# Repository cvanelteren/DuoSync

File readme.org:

* Welcome to Duosync - a BLE wireless split keyboard powered by ZMK
The keyboard is designed by me, and is a spirtual successor to [[https://github.com/cvanelteren/Elanor/][Elanor]].

[[file:./figures/duosync.jpg]]

* Bill Of Materials

|------------------------------------+----------+------------------|
| Item                               | Quantity | Price indication |
|------------------------------------+----------+------------------|
| XIAO BLE SEEED                     |        2 | 15$              |
| Kailh/Gateron hotswappable sockets |       52 | 12$              |
| Duosync PCB                        |        2 | 5$               |
| Keyswitches                        |       52 | 30$              |
| Battery Lithium ion 3.7V           |        2 | 15$              |
| Case                               |        2 | Depends ;-)       |
|------------------------------------+----------+------------------|

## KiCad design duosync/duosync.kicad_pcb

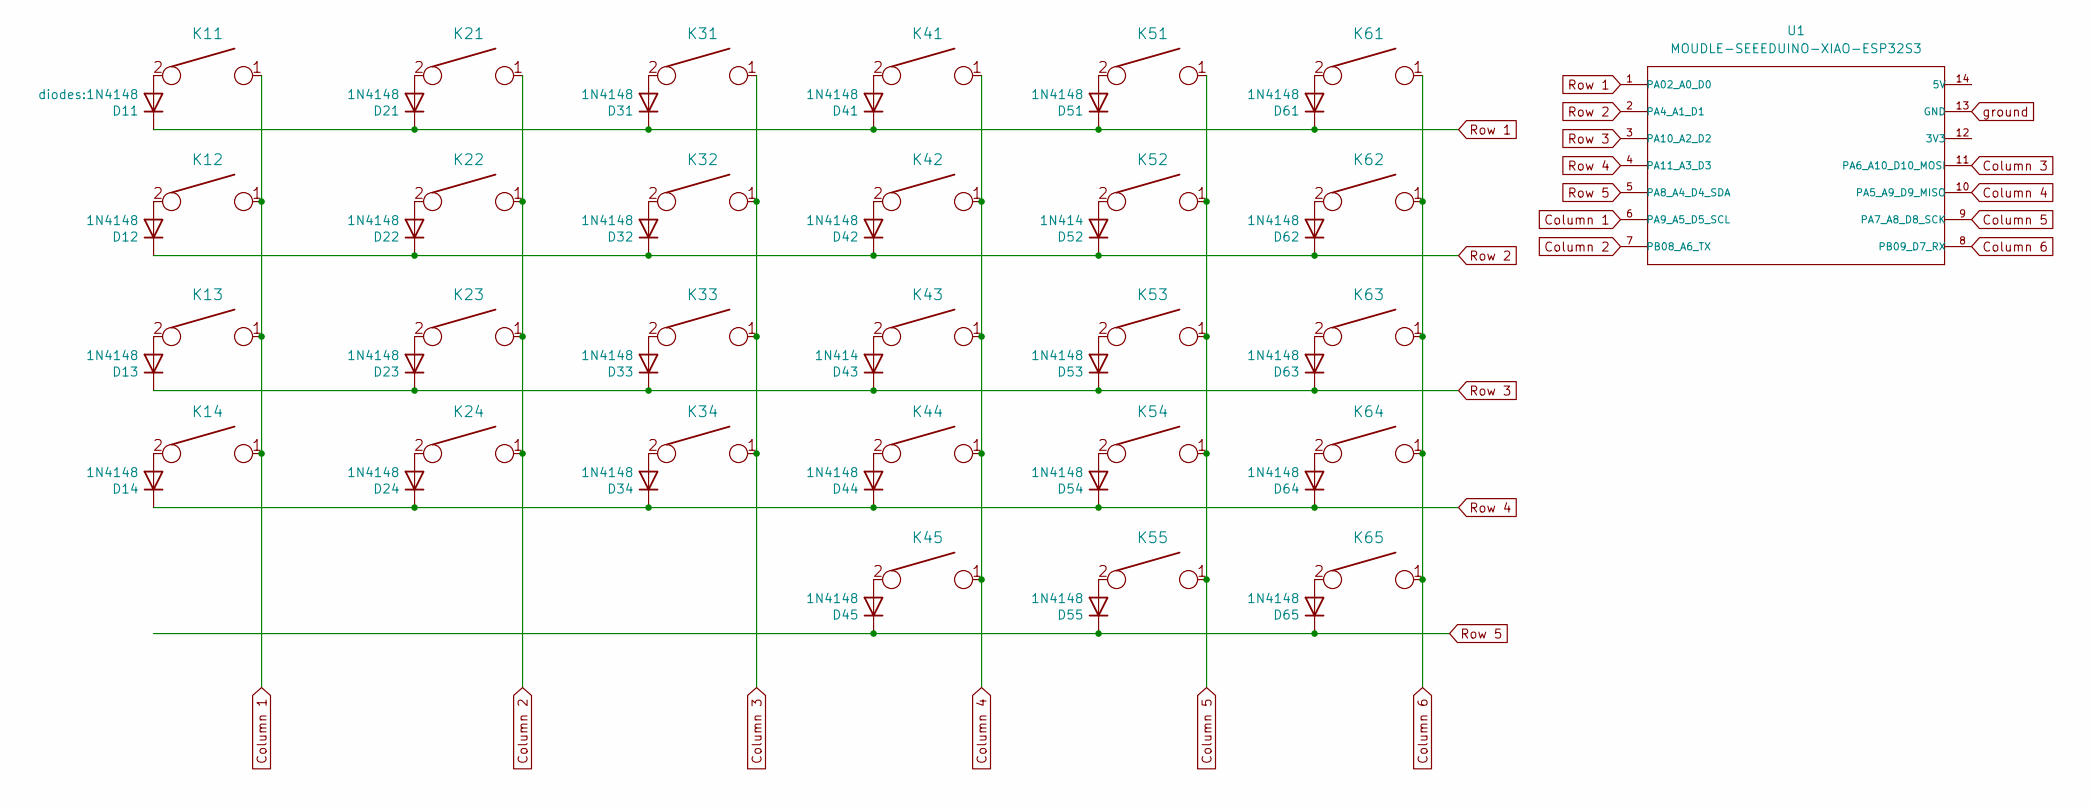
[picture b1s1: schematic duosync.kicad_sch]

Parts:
D11: diodes:1N4148; D3_TH_SMD_v2
D12, D13, D14, D21, D22, D23, D24, D31, D32, D33, D34, D41, D42, D44, D45, D51, D53, D54, D55, D61, D62, D63, D64, D65: 1N4148; D3_TH_SMD_v2
D43, D52: 1N414; D3_TH_SMD_v2
K11, K12, K13, K14, K21, K22, K23, K24, K31, K32, K33, K34, K41, K42, K43, K44, K45, K51, K52, K53, K54, K55, K61, K62, K63, K64: key; CherryMX_Choc_Hotswap
K65: key; CherryMX_Choc_Hotswap_1.5u
U1: MOUDLE-SEEEDUINO-XIAO-ESP32S3; XIAO-Generic-Hybrid-14P-2.54-21X17.8MM

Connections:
Column 1: K11.1, K12.1, K13.1, K14.1, U1.6 (PA9_A5_D5_SCL)
Column 2: K21.1, K22.1, K23.1, K24.1, U1.7 (PB08_A6_TX)
Column 3: K31.1, K32.1, K33.1, K34.1, U1.11 (PA6_A10_D10_MOSI)
Column 4: K41.1, K42.1, K43.1, K44.1, K45.1, U1.10 (PA5_A9_D9_MISO)
Column 5: K51.1, K52.1, K53.1, K54.1, K55.1, U1.9 (PA7_A8_D8_SCK)
Column 6: K61.1, K62.1, K63.1, K64.1, K65.1, U1.8 (PB09_D7_RX)
unnamed: D11.2 (A), K11.2
unnamed: D12.2 (A), K12.2
unnamed: D13.2 (A), K13.2
unnamed: D14.2 (A), K14.2
unnamed: D21.2 (A), K21.2
unnamed: D22.2 (A), K22.2
unnamed: D23.2 (A), K23.2
unnamed: D24.2 (A), K24.2
unnamed: D31.2 (A), K31.2
unnamed: D32.2 (A), K32.2
unnamed: D33.2 (A), K33.2
unnamed: D34.2 (A), K34.2
unnamed: D41.2 (A), K41.2
unnamed: D42.2 (A), K42.2
unnamed: D43.2 (A), K43.2
unnamed: D44.2 (A), K44.2
unnamed: D45.2 (A), K45.2
unnamed: D51.2 (A), K51.2
unnamed: D52.2 (A), K52.2
unnamed: D53.2 (A), K53.2
unnamed: D54.2 (A), K54.2
unnamed: D55.2 (A), K55.2
unnamed: D61.2 (A), K61.2
unnamed: D62.2 (A), K62.2
unnamed: D63.2 (A), K63.2
unnamed: D64.2 (A), K64.2
unnamed: D65.2 (A), K65.2
Row 1: D11.1 (K), D21.1 (K), D31.1 (K), D41.1 (K), D51.1 (K), D61.1 (K), U1.1 (PA02_A0_D0)
Row 2: D12.1 (K), D22.1 (K), D32.1 (K), D42.1 (K), D52.1 (K), D62.1 (K), U1.2 (PA4_A1_D1)
Row 3: D13.1 (K), D23.1 (K), D33.1 (K), D43.1 (K), D53.1 (K), D63.1 (K), U1.3 (PA10_A2_D2)
Row 4: D14.1 (K), D24.1 (K), D34.1 (K), D44.1 (K), D54.1 (K), D64.1 (K), U1.4 (PA11_A3_D3)
Row 5: D45.1 (K), D55.1 (K), D65.1 (K), U1.5 (PA8_A4_D4_SDA)
ground: U1.13 (GND)

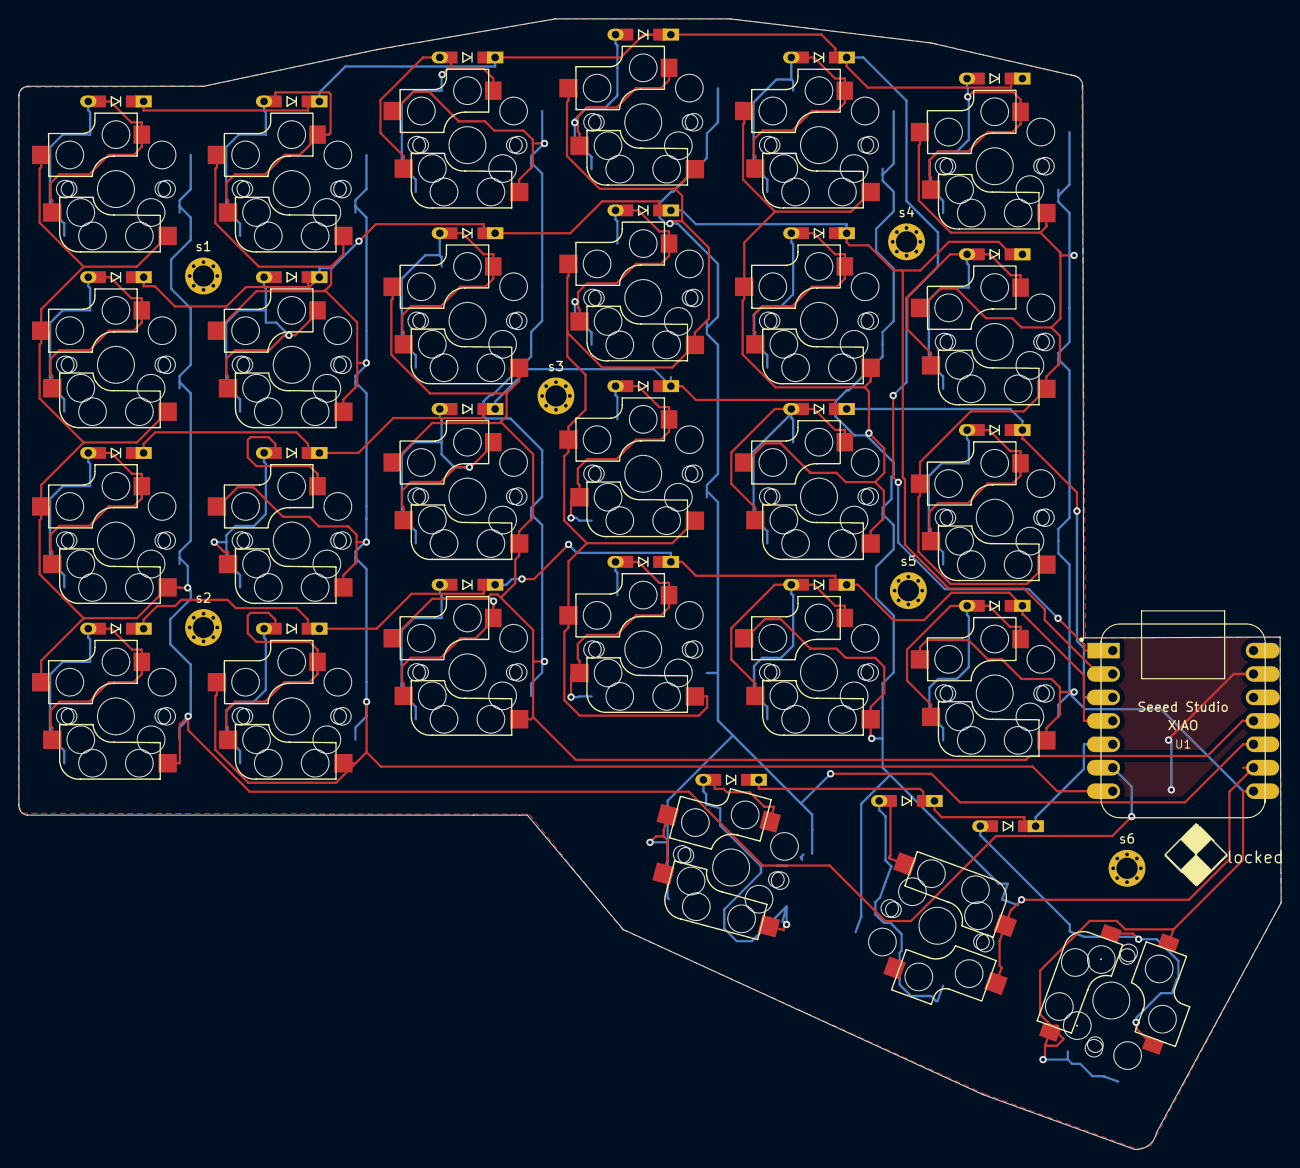
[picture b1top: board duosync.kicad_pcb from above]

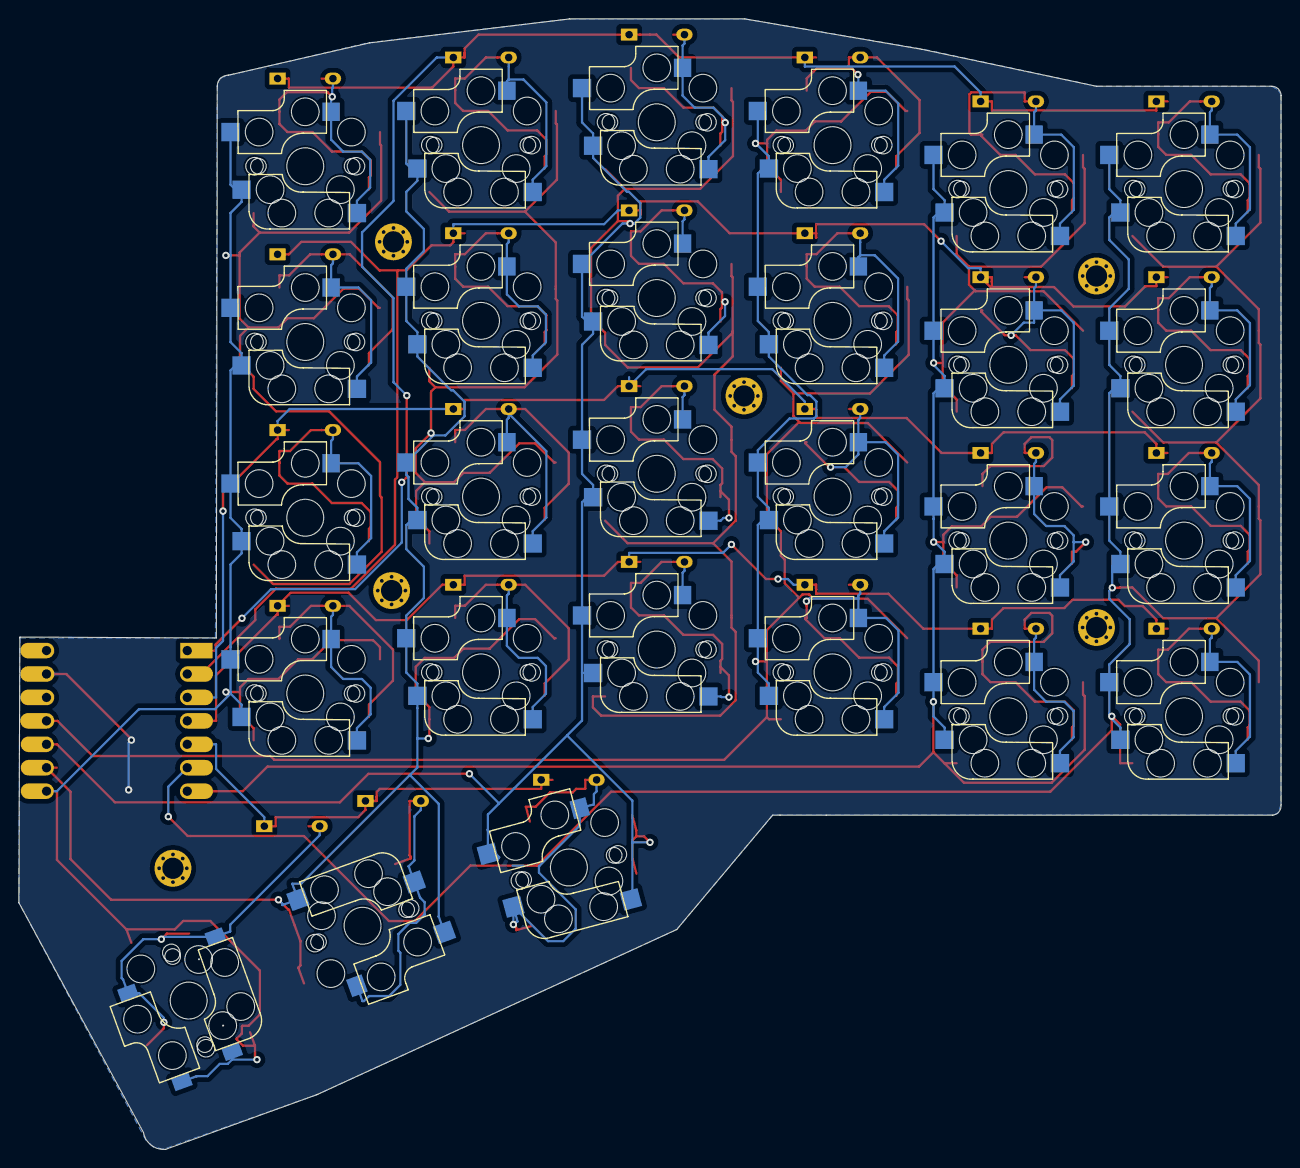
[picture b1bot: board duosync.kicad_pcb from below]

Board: 2 copper layers, 136.8 x 122.5 mm, 62 parts (2 on the bottom side), 38 nets.

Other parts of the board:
BOARD_LOGO1: locked; cve_logo_neg
s1, s2, s3, s4, s5, s6: Val**; M2_HOLE_v3

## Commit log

2024-03-17 ready for initial test
2024-03-21 added pcb v1.1
2024-03-21 added stls for case v1.01
2024-03-21 Fixed link
2024-03-21 added license
2024-03-21 Added welcome title
2024-03-30 added BoM
